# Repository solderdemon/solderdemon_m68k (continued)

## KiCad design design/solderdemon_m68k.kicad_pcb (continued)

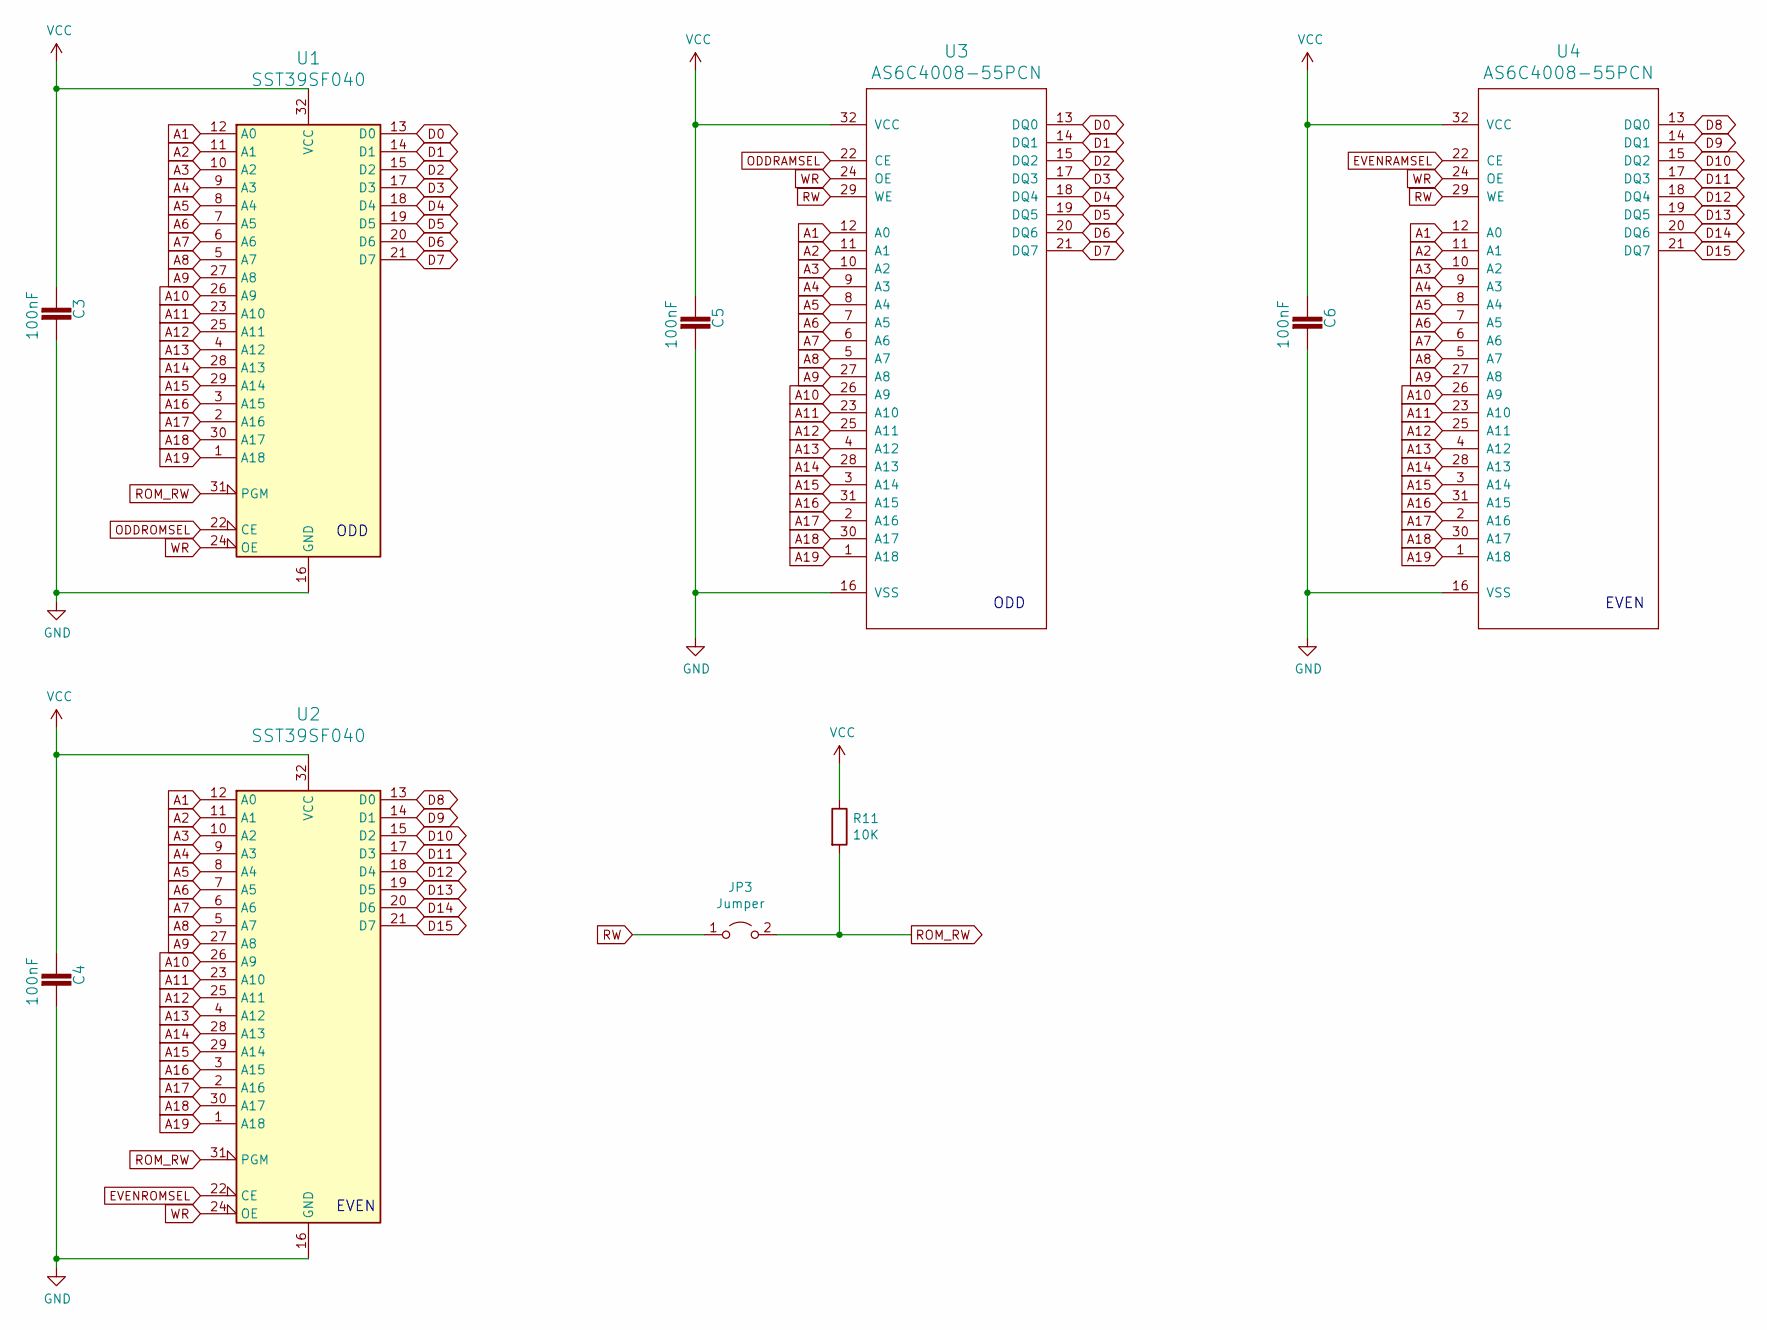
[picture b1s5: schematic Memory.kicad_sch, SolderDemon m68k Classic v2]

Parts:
C3, C4, C5, C6: 100nF; C_Radial_5.08mm
JP3: Jumper; 1X02
R11: 10K; 0207_10
U1, U2: SST39SF040; DIP-32_W15.24mm_LongPads
U3, U4: AS6C4008-55PCN; DIP-32_W15.24mm_LongPads

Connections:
A1: U1.12 (A0), U2.12 (A0), U3.12 (A0), U4.12 (A0); also elsewhere on the board
A2: U1.11 (A1), U2.11 (A1), U3.11 (A1), U4.11 (A1); also elsewhere on the board
A3: U1.10 (A2), U2.10 (A2), U3.10 (A2), U4.10 (A2); also elsewhere on the board
A4: U1.9 (A3), U2.9 (A3), U3.9 (A3), U4.9 (A3); also elsewhere on the board
A5: U1.8 (A4), U2.8 (A4), U3.8 (A4), U4.8 (A4); also elsewhere on the board
A6: U1.7 (A5), U2.7 (A5), U3.7 (A5), U4.7 (A5); also elsewhere on the board
A7: U1.6 (A6), U2.6 (A6), U3.6 (A6), U4.6 (A6); also elsewhere on the board
A8: U1.5 (A7), U2.5 (A7), U3.5 (A7), U4.5 (A7); also elsewhere on the board
A9: U1.27 (A8), U2.27 (A8), U3.27 (A8), U4.27 (A8); also elsewhere on the board
A10: U1.26 (A9), U2.26 (A9), U3.26 (A9), U4.26 (A9); also elsewhere on the board
A11: U1.23 (A10), U2.23 (A10), U3.23 (A10), U4.23 (A10); also elsewhere on the board
A12: U1.25 (A11), U2.25 (A11), U3.25 (A11), U4.25 (A11); also elsewhere on the board
A13: U1.4 (A12), U2.4 (A12), U3.4 (A12), U4.4 (A12); also elsewhere on the board
A14: U1.28 (A13), U2.28 (A13), U3.28 (A13), U4.28 (A13); also elsewhere on the board
A15: U1.29 (A14), U2.29 (A14), U3.3 (A14), U4.3 (A14); also elsewhere on the board
A16: U1.3 (A15), U2.3 (A15), U3.31 (A15), U4.31 (A15); also elsewhere on the board
A17: U1.2 (A16), U2.2 (A16), U3.2 (A16), U4.2 (A16); also elsewhere on the board
A18: U1.30 (A17), U2.30 (A17), U3.30 (A17), U4.30 (A17); also elsewhere on the board
A19: U1.1 (A18), U2.1 (A18), U3.1 (A18), U4.1 (A18); also elsewhere on the board
D0: U1.13 (D0), U3.13 (DQ0); also elsewhere on the board
D1: U1.14 (D1), U3.14 (DQ1); also elsewhere on the board
D2: U1.15 (D2), U3.15 (DQ2); also elsewhere on the board
D3: U1.17 (D3), U3.17 (DQ3); also elsewhere on the board
D4: U1.18 (D4), U3.18 (DQ4); also elsewhere on the board
D5: U1.19 (D5), U3.19 (DQ5); also elsewhere on the board
D6: U1.20 (D6), U3.20 (DQ6); also elsewhere on the board
D7: U1.21 (D7), U3.21 (DQ7); also elsewhere on the board
D8: U2.13 (D0), U4.13 (DQ0); also elsewhere on the board
D9: U2.14 (D1), U4.14 (DQ1); also elsewhere on the board
D10: U2.15 (D2), U4.15 (DQ2); also elsewhere on the board
D11: U2.17 (D3), U4.17 (DQ3); also elsewhere on the board
D12: U2.18 (D4), U4.18 (DQ4); also elsewhere on the board
D13: U2.19 (D5), U4.19 (DQ5); also elsewhere on the board
D14: U2.20 (D6), U4.20 (DQ6); also elsewhere on the board
D15: U2.21 (D7), U4.21 (DQ7); also elsewhere on the board
EVENRAMSEL: U4.22 (CE); also elsewhere on the board
EVENROMSEL: U2.22 (CE); also elsewhere on the board
GND: C3.2, C4.2, C5.2, C6.2, U1.16 (GND), U2.16 (GND), U3.16 (VSS), U4.16 (VSS); also elsewhere on the board
ODDRAMSEL: U3.22 (CE); also elsewhere on the board
ODDROMSEL: U1.22 (CE); also elsewhere on the board
ROM_RW: JP3.2 (B), R11.2, U1.31 (PGM), U2.31 (PGM)
RW: JP3.1 (A), U3.29 (WE), U4.29 (WE); also elsewhere on the board
VCC: C3.1, C4.1, C5.1, C6.1, R11.1, U1.32 (VCC), U2.32 (VCC), U3.32 (VCC), U4.32 (VCC); also elsewhere on the board
WR: U1.24 (OE), U2.24 (OE), U3.24 (OE), U4.24 (OE); also elsewhere on the board

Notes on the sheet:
EVEN
ODD

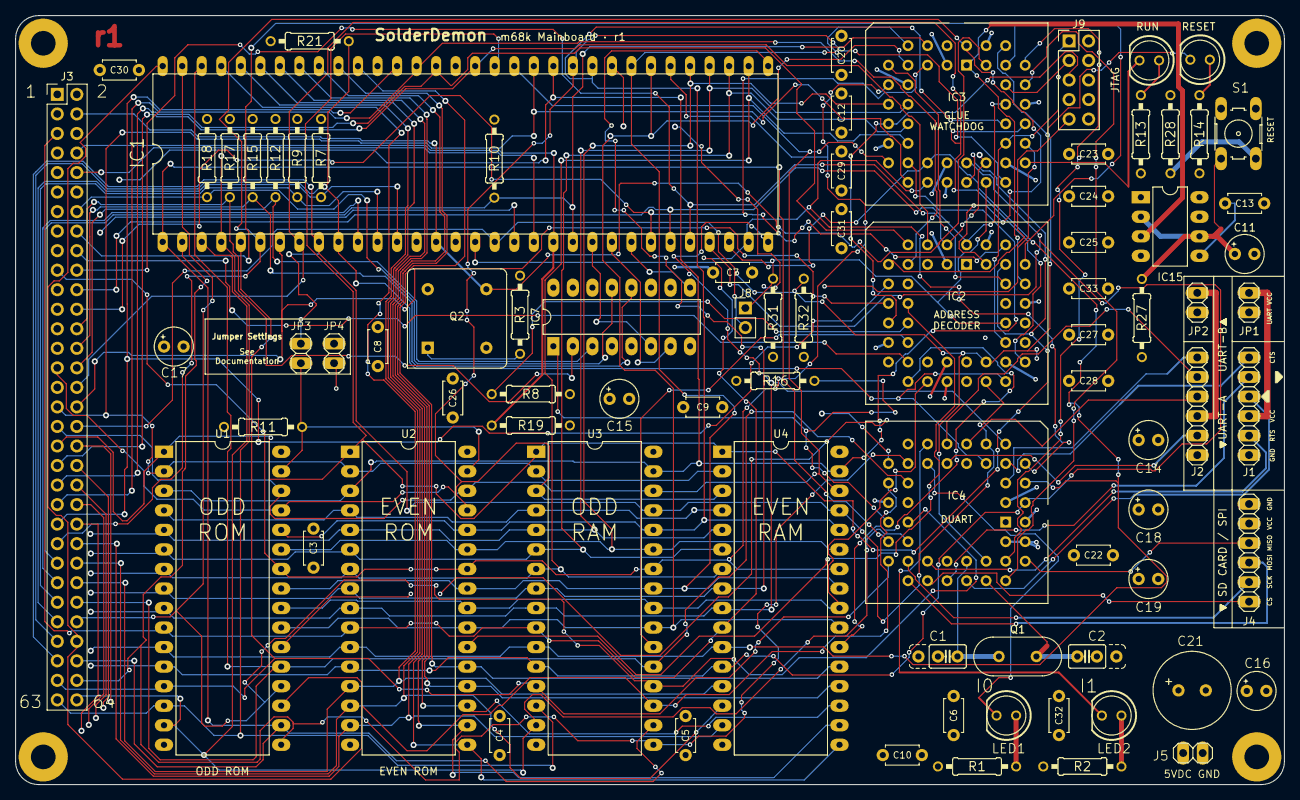
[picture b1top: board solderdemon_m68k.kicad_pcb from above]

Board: 4 copper layers, 165.0 x 100.0 mm, 87 parts (1 on the bottom side), 111 nets.

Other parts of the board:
C11: 100uF; E2,5-5
C13: 100nF; C_Radial_5.08mm
IC15: 555N; DIP-8_W7.62mm_LongPads
LED3: GREEN; LED5MM
LED4: RED; LED5MM
LOGO1: SolderDemon_Logo
R13, R14: 330R; 0207_10
R27: 2K2; 0207_10
R28: 270R; 0207_10
R31, R32: 4K7; 0207_10
S1: 10-XX; B3F-10XX

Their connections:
GND: C11.-, IC15.1 (GND), R28.1; also elsewhere on the board
HALT: R31.1; also elsewhere on the board
HWRST: IC15.3 (Q); also elsewhere on the board
unnamed: C13.2, IC15.5 (CV)
unnamed: C11.+, IC15.2 (TR), IC15.6 (THR), R27.1, S1.1 (S)
unnamed: LED3.A, R13.1
unnamed: LED4.A, R14.1
unnamed: R28.2, S1.3
RESET: LED4.K (C), R32.1; also elsewhere on the board
RUNLED: LED3.K (C); also elsewhere on the board
VCC: C13.1, IC15.4 (R), IC15.8 (V+), R13.2, R14.2, R27.2, R31.2, R32.2; also elsewhere on the board

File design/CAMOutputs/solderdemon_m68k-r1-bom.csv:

"Refs","Value","Footprint","Qty","DNP"
"C1,C2","7pF","rosco_m68k:C2.5_or_3.5-3","2",""
"C3-C10,C12,C13,C20,C22-C33","100nF","rosco_m68k:C2.5-3","23",""
"C11,C14-C19","100uF","rosco_m68k:E2,5-5","7",""
"C21","470uF","rosco_m68k:E3,5-10","1",""
"H1-H4","MountingHole","MountingHole:MountingHole_3.2mm_M3_Pad","4",""
"IC1","MC68010P10","rosco_m68k:DIL64","1",""
"IC2,IC3","ATF1502AS-10JU44","Package_LCC:PLCC-44_THT-Socket","2",""
"IC4","XR68C681CJTR-F","Package_LCC:PLCC-44_THT-Socket","1",""
"IC7","74LS148","Package_DIP:DIP-16_W7.62mm_LongPads","1",""
"IC15","555N","Package_DIP:DIP-8_W7.62mm_LongPads","1",""
"J1","UART_A","rosco_m68k:1X06","1",""
"J2","UART_B","rosco_m68k:1X06","1",""
"J3","Conn_02x32_Odd_Even","Connector_PinHeader_2.54mm:PinHeader_2x32_P2.54mm_Vertical","1",""
"J4","Conn_01x06","rosco_m68k:1X06","1",""
"J5","PWR","rosco_m68k:1X02","1",""
"J8","Conn_01x02_Male","Connector_PinHeader_2.54mm:PinHeader_1x02_P2.54mm_Vertical","1",""
"J9","JTAG","Connector_PinHeader_2.54mm:PinHeader_2x05_P2.54mm_Vertical","1",""
"JP1-JP4","Jumper","rosco_m68k:1X02","4",""
"LED1,LED3","GREEN","rosco_m68k:LED5MM","2",""
"LED2,LED4","RED","rosco_m68k:LED5MM","2",""
"Q1","3.6864MHz","Crystal:Crystal_HC49-4H_Vertical","1",""
"Q2","5H8ET-10.000","Oscillator:Oscillator_DIP-8","1",""
"R1,R2,R13,R14","330R","rosco_m68k:0207_10","4",""
"R3,R7-R10,R12,R15-R18,R31,R32","4K7","rosco_m68k:0207_10","12",""
"R11,R19","10K","rosco_m68k:0207_10","2",""
"R21","1K2","rosco_m68k:0207_10","1",""
"R27","2K2","rosco_m68k:0207_10","1",""
"R28","270R","rosco_m68k:0207_10","1",""
"S1","10-XX","rosco_m68k:B3F-10XX","1",""
"U1,U2","SST39SF040","Package_DIP:DIP-32_W15.24mm_LongPads","2",""
"U3,U4","AS6C4008-55PCN","Package_DIP:DIP-32_W15.24mm_LongPads","2",""

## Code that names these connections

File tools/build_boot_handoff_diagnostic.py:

"""Generate an isolated IC2 experiment: end ROM overlay on a high-ROM read.

Does not count AS edges during vector fetch. Intended only for ROM firmware
whose reset PC is in E00000-EFFFFF. No physical timing claim is made.
"""
from pathlib import Path
import random
import sys
import zipfile

import cupl


ROOT = Path(__file__).resolve().parents[1] / 'code/firmware/pld/cpld'
OUT = ROOT / 'diagnostics/boot_handoff'
LEGACY = ROOT / 'diagnostics/legacy_as_counter'


def pins(dev, address=0):
    p = {n: 0 for n in dev.pins.values()}
    p.update(HALT=1, RESET=1, HWRST=0, AS=0, RW=1, LGEXP=1, FC2=1, FC0=1)
    for bit in (19, 20, 21, 22, 23):
        p[f'A{bit}'] = address >> bit & 1
    return p


def generate():
    OUT.mkdir(parents=True, exist_ok=True)
    baseline = LEGACY if LEGACY.exists() else ROOT
    source = (baseline / 'ic2_decoder.pld').read_text()
    source = source.replace('PINNODE = [BQ0..2];                 /* boot counter */\n', '')
    marker = '/* BOOT is cleared while RESET and HALT are both asserted'
    assert source.count(marker) == 1
    candidate = source.split(marker)[0] + '''/* Diagnostic experiment: keep the ROM overlay throughout reset-vector
   reads. End it after the first normal read in E00000-EFFFFF, where the
   existing firmware is linked. Extra AS edges at low addresses do not
   advance a counter. BOOT stays set until external RESET+HALT. */
running = HALT # RESET;
highrom = A23 & A22 & A21 & !A20;
BOOT.d  = running & (BOOT # (ANYIACK & RW & highrom));
BOOT.ck = AS;
BOOT.ar = !HALT & !RESET;
'''
    assert 'BQ0' not in candidate and 'BQ1' not in candidate and 'BQ2' not in candidate
    original = cupl.Device((baseline / 'ic2_decoder.pld').read_text())
    dev = cupl.Device(candidate)

    # Any number of extra low-address AS edges must leave the vector ROM mapped.
    for initial in (0, 1):
        q = {'BOOT': initial}
        p = pins(dev); p.update(HALT=0, RESET=0, HWRST=1)
        dev.outputs(p, q)
        assert q == {'BOOT': 0}
        for extra in range(65):
            for address in (0, 2, 4, 6):
                p = pins(dev, address)
                for _ in range(extra + 1):
                    o = dev.outputs(p, q)
                    assert o['EVENROMSEL'] == o['ODDROMSEL'] == 0
                    assert o['EVENRAMSEL'] == o['ODDRAMSEL'] == 1
                    q = dev.clock_edge(p, q, {'AS'})
                    assert q['BOOT'] == 0
        p = pins(dev, 0xE00404)
        assert dev.outputs(p, q)['EVENROMSEL'] == 0
        q = dev.clock_edge(p, q, {'AS'})
        assert q['BOOT'] == 1
        p = pins(dev, 0)
        o = dev.outputs(p, q)
        assert o['EVENRAMSEL'] == o['ODDRAMSEL'] == 0
        assert o['EVENROMSEL'] == o['ODDROMSEL'] == 1

    # Memory decoding itself remains identical at either value of BOOT.
    rng = random.Random(1)
    for _ in range(20000):
        p = {n: rng.getrandbits(1) for n in original.pins.values()}
        boot = rng.getrandbits(1)
        q_old = {r: rng.getrandbits(1) for r in original.regs}; q_old['BOOT'] = boot
        assert original.outputs(p, q_old) == dev.outputs(p, {'BOOT': boot})
    # Demonstrate the hypothesized failure with one extra vector AS edge.
    q_old = original.reset_state(); p = pins(original)
    for _ in range(4):
        q_old = original.clock_edge(p, q_old, {'AS'})
    assert original.outputs(p, q_old)['EVENRAMSEL'] == 0
    print('PASS: extra low-address edges do not remove vector ROM; high-ROM read ends overlay.')
    print('PASS: 20,000 random decode vectors agree at the same BOOT state.')
    print('Model reproduces early RAM selection after an extra AS edge in the original counter.')
    (OUT / 'ic2_decoder.pld').write_text(candidate)
    (OUT / 'ic3_glue.pld').write_bytes((ROOT / 'ic3_glue.pld').read_bytes())
    (OUT / 'build.sh').write_text((ROOT / 'build.sh').read_text().replace('python - ', 'python3 - '))
    (OUT / 'README.md').write_text('''# Boot-handoff experiment

Generated by tools/build_boot_handoff_diagnostic.py.
This is an unconfirmed diagnostic hypothesis, not a proven repair.

IC2 replaces the four-AS-edge boot counter with a sticky BOOT register set
at the end of the first normal read in E00000-EFFFFF. This requires the
reset PC to point into high ROM, as the existing rosco firmware linker does.
The low-address vector ROM cannot disappear due solely to extra low-address
AS edges. No wait states are added. All external pins retain their assignments.

IC3 in this experiment is the ORIGINAL production image, not reset_guard.
Build with bash build.sh; check the fit with check_startup_fit.py pointing
at this directory. The original checker still compares production sources
against GALs; this experiment intentionally changes BOOT timing.

For an isolated hardware test, program IC2_TEST.jed into IC2 and
IC3_ORIGINAL.jed into IC3. Verify both. ROM Flash contents remain unchanged.
Rollback IC2 using IC2_ROLLBACK.jed. Do not exchange these chip assignments.

Source-model checks cover reset from both BOOT states, up to 64 extra AS
edges per vector word, high-ROM handoff, RAM selection and 20,000 random
decode vectors. These checks do not prove that AS ringing occurs on the board,
or that timing, voltage or physical connections are correct.
''')
    print(OUT)


def package():
    paths = {'IC2_TEST.jed': OUT / 'bin/ic2_decoder.jed',
             'IC3_ORIGINAL.jed': ROOT / 'bin/ic3_glue.jed',
             'IC2_ROLLBACK.jed': (LEGACY if LEGACY.exists() else ROOT) / 'bin/ic2_decoder.jed',
             'ic2_decoder.pld': OUT / 'ic2_decoder.pld',
             'ic2_decoder.fit': OUT / 'bin/ic2_decoder.fit',
             'README.md': OUT / 'README.md'}
    target = OUT / 'solderdemon_m68k-boot-handoff-test.zip'
    with zipfile.ZipFile(target, 'w', zipfile.ZIP_DEFLATED) as z:
        for name, path in paths.items():
            z.writestr(name, path.read_bytes())
    print(target)


if __name__ == '__main__':
    if sys.argv[1:] == ['--package']:
        package()
    elif not sys.argv[1:]:
        generate()
    else:
        raise SystemExit('Usage: build_boot_handoff_diagnostic.py [--package]')

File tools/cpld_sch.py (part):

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CPLD_LIB = 'rosco_m68k:ATF1502AS-xJx44'
PLCC = 'Package_LCC:PLCC-44_THT-Socket'
VCC_PINS, GND_PINS = (3, 15, 23, 35), (10, 22, 30, 42)
JTAG_PINS = {7: 'JTAG_TDI', 13: 'JTAG_TMS', 32: 'JTAG_TCK', 38: 'JTAG_TDO'}
# TDI of the header goes to IC2, IC2's TDO to IC3's TDI, IC3's TDO back to the header
JTAG_CHAIN = {'IC2': {38: 'JTAG_CHAIN'}, 'IC3': {7: 'JTAG_CHAIN'}}
CHIPS = {  # ref: (CUPL source, uuid kept from r2.13, position)
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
